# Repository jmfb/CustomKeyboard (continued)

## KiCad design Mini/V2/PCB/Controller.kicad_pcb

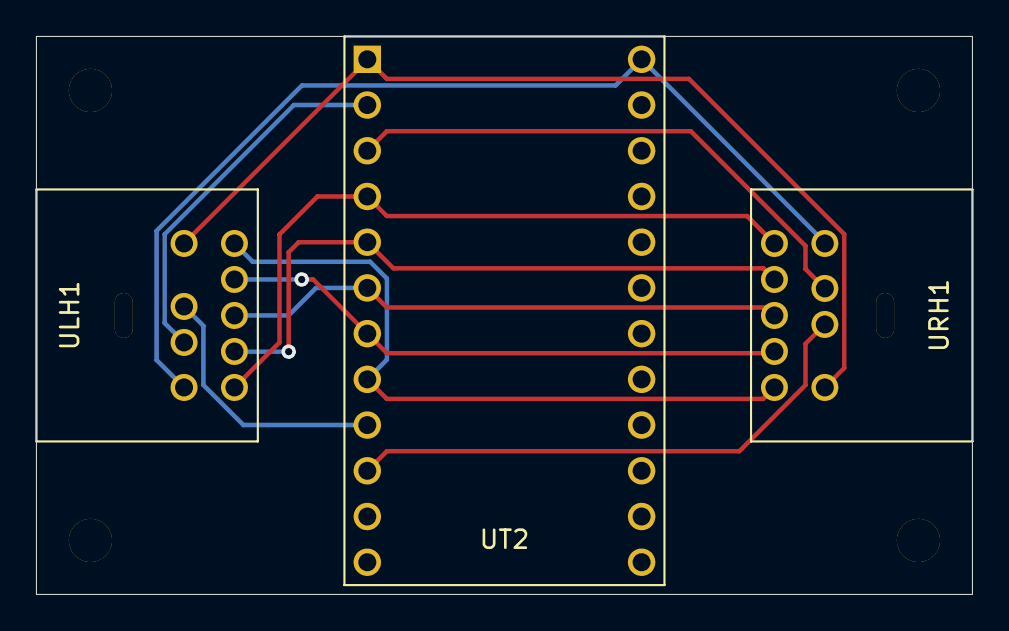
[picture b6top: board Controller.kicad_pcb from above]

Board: 2 copper layers, 52.0 x 31.0 mm, 3 parts (0 on the bottom side), 11 nets.

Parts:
ULH1: MiniDINN9; MiniDin9
URH1: MiniDINN9; MiniDin9
UT2: Teensy2.0

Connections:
unnamed: ULH1.1, UT2.2
unnamed: ULH1.2, UT2.9
unnamed: ULH1.3, URH1.3, UT2.24
unnamed: ULH1.4, URH1.4, UT2.5
unnamed: ULH1.5, URH1.5, UT2.6
unnamed: ULH1.6, URH1.6, UT2.1
unnamed: ULH1.7, URH1.7, UT2.4
unnamed: ULH1.8, URH1.8, UT2.7
unnamed: ULH1.9, URH1.9, UT2.8
unnamed: URH1.1, UT2.3
unnamed: URH1.2, UT2.10

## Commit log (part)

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2015-12-08 :tada: Added .gitattributes
2015-12-08 Adding custom keyboard files.
    Adding mounting plate OpenSCAD files, PCB KiCAD files, and Arduino
    (Teensy) program.
2017-11-24 Updating dxf exports to use blue lines.
2017-11-25 Adding faceplate templates.
2017-11-25 Adding base plates.
2017-11-25 Adding case parts for left hand board.
2017-11-26 Fixing lhr. Adding right hand/accessory case.
2017-11-26 Re-exporting rha left!
2017-11-28 Switching left hand spacebar into hyper key.
2017-12-01 Rewriting keyboard logic for proper hyperkey.
2017-12-01 Finishing hyperkey version and adding tests.
2017-12-01 Turning off cmd echo.
2017-12-02 Moving C++ files to Controller subfolder.
2017-12-02 Adding more unit tests and fixed a couple bugs.
2017-12-08 Adding program to compute layouts.
2017-12-10 Initial left hand v4 PCB.
2017-12-11 V4 base plates, initial controller PCB.
2017-12-12 Left Hand V4 PCB w/ stabilizers.
2017-12-13 Generating gerber files for LeftHand and Controller.
2017-12-14 Upgraded to latest KiCad, added RightHand PCB.
2017-12-14 Finished RightHandV4 board and Gerber exports.
2017-12-14 Working on face plates and mounting plates.
2017-12-15 Finishing stabilizer cutouts. Adding connector art.
2017-12-16 Adding readme.
2017-12-18 Adding images for V1-3.
2018-01-05 Fixing a bug for the record books by adding delay(1).
2018-01-13 Updated readme for V4 lessons learned.
2018-01-13 Adding V5 design notes to readme.
2018-01-13 Layout, mounting plates, and faceplates for V5.
2018-01-14 Base plates for V5.
2018-01-14 V5 Left Hand PCB.
2018-01-14 V5 Right Hand PCB.
2018-01-21 V5 controller.
2020-09-22 Adding V3 controller with hyper key turned off.
2020-09-22 Fixing unsigned/int narrowing conversion warnings.
2021-05-21 Adding color to scad files.
2021-05-21 Pushing updated DXF exports.
2021-05-21 LED keys, resistors, and diodes pictures for V5.
2021-06-19 Adding readme and scad files for Mini V1.
2021-06-19 Adding wristpad part.
2021-06-20 Fixing thumb 2-key faceplate cutout.
2021-06-20 Adding rounded thumb-side bottom corner to wrist pad.
2021-06-21 Adding keycap parts to readme.
2021-06-21 Refactoring to use finger column array.
2021-06-21 Fixing connector positioning and finishing correct PCB layout (with PCB spacing test for verification).
2021-06-21 Finishing stabilizers for mounting plate.
2021-06-21 Removing pegs (probably not needed, fingers crossed). Adding 0.5mm padding to connector to prevent rub.
2021-06-21 Re-exporting all layers after updates.
2021-06-22 Updating screw sizes.
2021-06-23 Adding back peg holes (only 2 so far).
2021-06-23 Adding remaining peg holes at key corners. Adding back in peg template.
2021-06-26 Adding keyswitch pin receptacles to readme.
2021-06-27 Playing with KiCad again.
2021-06-27 Setting up right hand PCB edge.
2021-06-27 Adding schematics for demux, register, and dinn9. Adding all components to schematic.
2021-06-28 Adding R2L/L2R and 2key variants of key footprints.
2021-06-28 Adding microchip and resistor footprints.
2021-06-28 Wiring up all pins on schematic.
2021-06-28 Switching some pins to passive and generating netlist.
2021-06-28 Laying out pcb.
2021-06-28 Moving some 2-key holes around.
2021-06-28 Adding extra 3mm to edge of thumb 2-keys to account for stabilizer holes on PCB.
2021-06-28 Updating PCB to account for new 3mm thumb 2-key spacing.
2021-06-29 Updating component footprints for proper silkscreen. Adding LED cutouts to PCB (except for 2-key).
2021-06-29 Adding thumb 2-key LED cutout computation to SCAD and putting them in PCB.
2021-06-29 Adding a bunch of wiring.
2021-06-29 Wiring everything except LED VCC/GND.
2021-06-29 Wiring up LED VCC.
2021-06-29 Generating gerber files and drill file.
2021-06-29 Moving gerber files to subdirectory. Renaming project files to RightHand (will also have LeftHand and Controller).
2021-06-29 Whoops. Missed the untracked files.
2021-06-29 Adding initial LeftHand project (filled in schematic components).
2021-07-02 Wiring left hand schematic, adding footprints, and generating netlist.
2021-07-02 Adding components to PCB. Fixing T2 footprints. Still need wiring and holes.
2021-07-03 Left hand edge cuts for LEDs and pegs.
2021-07-03 Finished wiring left hand. Generated gerber files.
2021-07-03 Adding scad for controller box.
2021-07-03 Controller PCB.
2021-07-03 Re-exporting DXF files.
2021-07-04 Initial commit for Mini controller. Just does stable key scanning for now.
2021-07-05 Updating readme with laser cut parts and PCBs.
2021-07-06 Refactor LayerKey to use less space.
2021-07-06 Adding example LED color code.
2021-07-06 Adding basic LED driver.
2021-07-07 Typo
2021-07-07 Adding more colors but commenting out unused ones. Fixing comment warning.
2021-07-07 Switching colors to constexpr to reduce global variable space used.
2021-07-07 Switching remaining global constants over to constexpr.
2021-07-09 Adding layer 4 (left hand while right hand is on mouse for backspace, enter, and arrow keys).
2021-07-09 Adding pulsate and transition logic to LED colors. Still no clue how it will look.
2021-07-09 Adding more tests. Found another bug!
2021-07-09 Adding more tests. Found another bug.
2021-07-11 Refactoring tests to use hand/finger enums.
2021-07-11 Adding full layer keymap tests.
2021-07-11 Adding failing test for layer key scenarios with keys pressed in rapid succession.
2021-07-11 Fixing case when pressing layer keys in rapid succession where the previous layer key had keyCode modifiers applied.
2021-07-11 Fixing layer issue with rapid succession keys with the same keyCode.
2021-07-11 Adding layout html file.
2021-07-15 Actual RGB LEDs are BGR (as in PDF) not RBG (as Greg's breakouts were).
2021-07-17 Updating layer colors.
2021-07-18 Adding more colors and led position enum.
2021-07-21 Switching delays to microseconds and updating pulse computation.
2021-07-21 Slowing down pulsate even more.
2021-08-10 Fixing tests broken when switching to microsecond delays.
2021-08-10 Adding screenshot key to layer 3.
2021-08-10 Adding early release from layer 3 when followed by a space (semicolon followed by space in rapid succession).
2021-08-12 Adding a layer 5 so I can do left hand only functions more easily.
2021-08-12 Lowering the held threshold to improve erroneous layer shift key insertion on layer abort. Slower key presses may no longer register.
2021-08-12 Removing redundant forward slash and moving backslash to layer 2 on the slash (same key is forward and back).
2021-08-12 Making layer 4 left hand function keys and moving backspace/enter to index extra column.
2021-08-12 Updating layout image.
2021-08-13 Moving mini artifacts into V1 subfolder. Adding an initial V2 copy.
2021-08-13 Switching input to pullup and lowering delay per docs.
2021-08-13 Backporting controller fix to V1.
2021-08-13 Fixing controller lid/wall height, hex padding, connector notch, peg inner height.
2021-08-13 Adding cutouts for dial inline chips in the mounting plate.
2021-08-13 Adding connector notch padding back in. I will move the connector up 0.5mm on the PCB instead to correct the mistake.
2021-08-13 Apparently updated some cache thingy.
2021-08-13 Re-exporting V2 DXF files.
2021-08-17 Updating V2 controller PCB to have 1mm holes for Teensy.
2021-08-17 Updating LH PCB register to read 01 for register[4..5] and RH to read 10. V1 will read as 00 for controller logic backward compatibility.
2021-08-17 Updating keyswitch footprints to increase LED width to 5.4mm and adding edge cuts (manually, per forum).
2021-08-19 Adding initial LED algorithm tester.
2021-08-19 Fixing some more wires.
2021-08-19 Adding a failing test for rapid unshift (still need to fix the controller to handle this case).
2021-08-19 Fixing dead layer key controller issue. Also fixed second SHIFT report from layer 5.
2021-08-20 Finished fixing LED hole wiring adjustments.
2021-08-20 Moving connector up 0.5mm.
2021-08-20 Fixing peg holes to be slightly wider (0.2mm on each side).
2021-08-20 Fixing wiring from peg hole increase. Regenerating gerber files for left hand.
2021-08-20 Putting back in support for shift held during layer transitions.
2021-08-20 Adding tests for V1 backwards compatibility and V2 inverted hands.
2021-08-20 Handling hardware being inverted. Not handling stupid permutations (two left hands, etc.) specially. LED output will follow most recent hand inversion reading.
2021-08-21 Getting initial webpack to build.
2021-08-29 Adding some more led code.
2021-08-29 Adding full led layout and initial completely random led pattern algorithm.
2021-09-01 Whoops. Must have inverted the hardware wiring for the sides.
2021-09-10 Switching random led algorithm to smooth linear hsl (angular) color transition.
2021-09-24 Starting to add more color modes. Have an 8-bit overflow issue.
2021-11-02 Inlining TestKey function in preparation for splitting modifier and key reports for layer keys with modifiers.
2021-11-02 Sending modifier keys separate from keycode for layer keys (to work better with RDP).
2021-12-15 Adding test for stupid lambda semicolon issue and fixing it.
2022-01-29 Adding test for rapid number transition while still holding layer 0 keys (took me a while for my typing speed to get fast enough to find this bug).
2022-03-30 Bump minimist from 1.2.5 to 1.2.6 in /Mini/LED
    Bumps [minimist](https://github.com/substack/minimist) from 1.2.5 to 1.2.6.
    - [Release notes](https://github.com/substack/minimist/releases)
    - [Commits](https://github.com/substack/minimist/compare/1.2.5...1.2.6)
    ---
    updated-dependencies:
    - dependency-name: minimist
2022-07-20 Bump terser from 5.7.1 to 5.14.2 in /Mini/LED
    Bumps [terser](https://github.com/terser/terser) from 5.7.1 to 5.14.2.
    - [Release notes](https://github.com/terser/terser/releases)
    - [Changelog](https://github.com/terser/terser/blob/master/CHANGELOG.md)
    - [Commits](https://github.com/terser/terser/commits)
    ---
    updated-dependencies:
2022-11-14 Bump loader-utils from 1.4.0 to 1.4.2 in /Mini/LED
    Bumps [loader-utils](https://github.com/webpack/loader-utils) from 1.4.0 to 1.4.2.
    - [Release notes](https://github.com/webpack/loader-utils/releases)
    - [Changelog](https://github.com/webpack/loader-utils/blob/v1.4.2/CHANGELOG.md)
    - [Commits](https://github.com/webpack/loader-utils/compare/v1.4.0...v1.4.2)
    ---
    updated-dependencies:
2023-03-06 Bump minimist from 1.2.5 to 1.2.8 in /Mini/LED
    Bumps [minimist](https://github.com/minimistjs/minimist) from 1.2.5 to 1.2.8.
    - [Release notes](https://github.com/minimistjs/minimist/releases)
    - [Changelog](https://github.com/minimistjs/minimist/blob/main/CHANGELOG.md)
    - [Commits](https://github.com/minimistjs/minimist/compare/v1.2.5...v1.2.8)
    ---
    updated-dependencies:
2023-03-14 Bump webpack from 5.45.1 to 5.76.0 in /Mini/LED
    Bumps [webpack](https://github.com/webpack/webpack) from 5.45.1 to 5.76.0.
    - [Release notes](https://github.com/webpack/webpack/releases)
    - [Commits](https://github.com/webpack/webpack/compare/v5.45.1...v5.76.0)
    ---
    updated-dependencies:
    - dependency-name: webpack
2024-02-04 Starting models for V3.
2024-02-04 Model for entire home row.
2024-02-04 Adding bent bottom row.
2024-02-04 Whoops to some naming issues after debugging.
2024-02-04 Adding top row.
2024-02-05 Fixing top/bottom inversion.
2024-02-08 Adding comments.
2024-02-08 Extending diagonal portion.
2024-02-08 Starting to add bottom row wall. Join is not perfect - need to diagnose.
2024-02-10 Fixed pinky lower row wall.
2024-02-10 Adding ring finger bottom row wall.
2024-02-10 Adding middle finger bottom row wall.
2024-02-10 Bottom row index finger wall. Bottom row wall done.
2024-02-10 Adding pinky plus one column. May need to rework mounting place spacing between keys.
2024-02-10 Top row index finger wall.
2024-02-10 Top row wall pinky.
2024-02-14 Working on the vertical column walls.
2024-02-14 Got pinky near vertical wall figured out. Next up: subtracting ring finger far vertical wall.
2024-02-16 Adding cutout. One wall done.
